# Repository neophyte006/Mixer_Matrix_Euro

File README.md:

View this project on [CADLAB.io](https://cadlab.io/project/1232). 

# Mixer_Matrix_Euro

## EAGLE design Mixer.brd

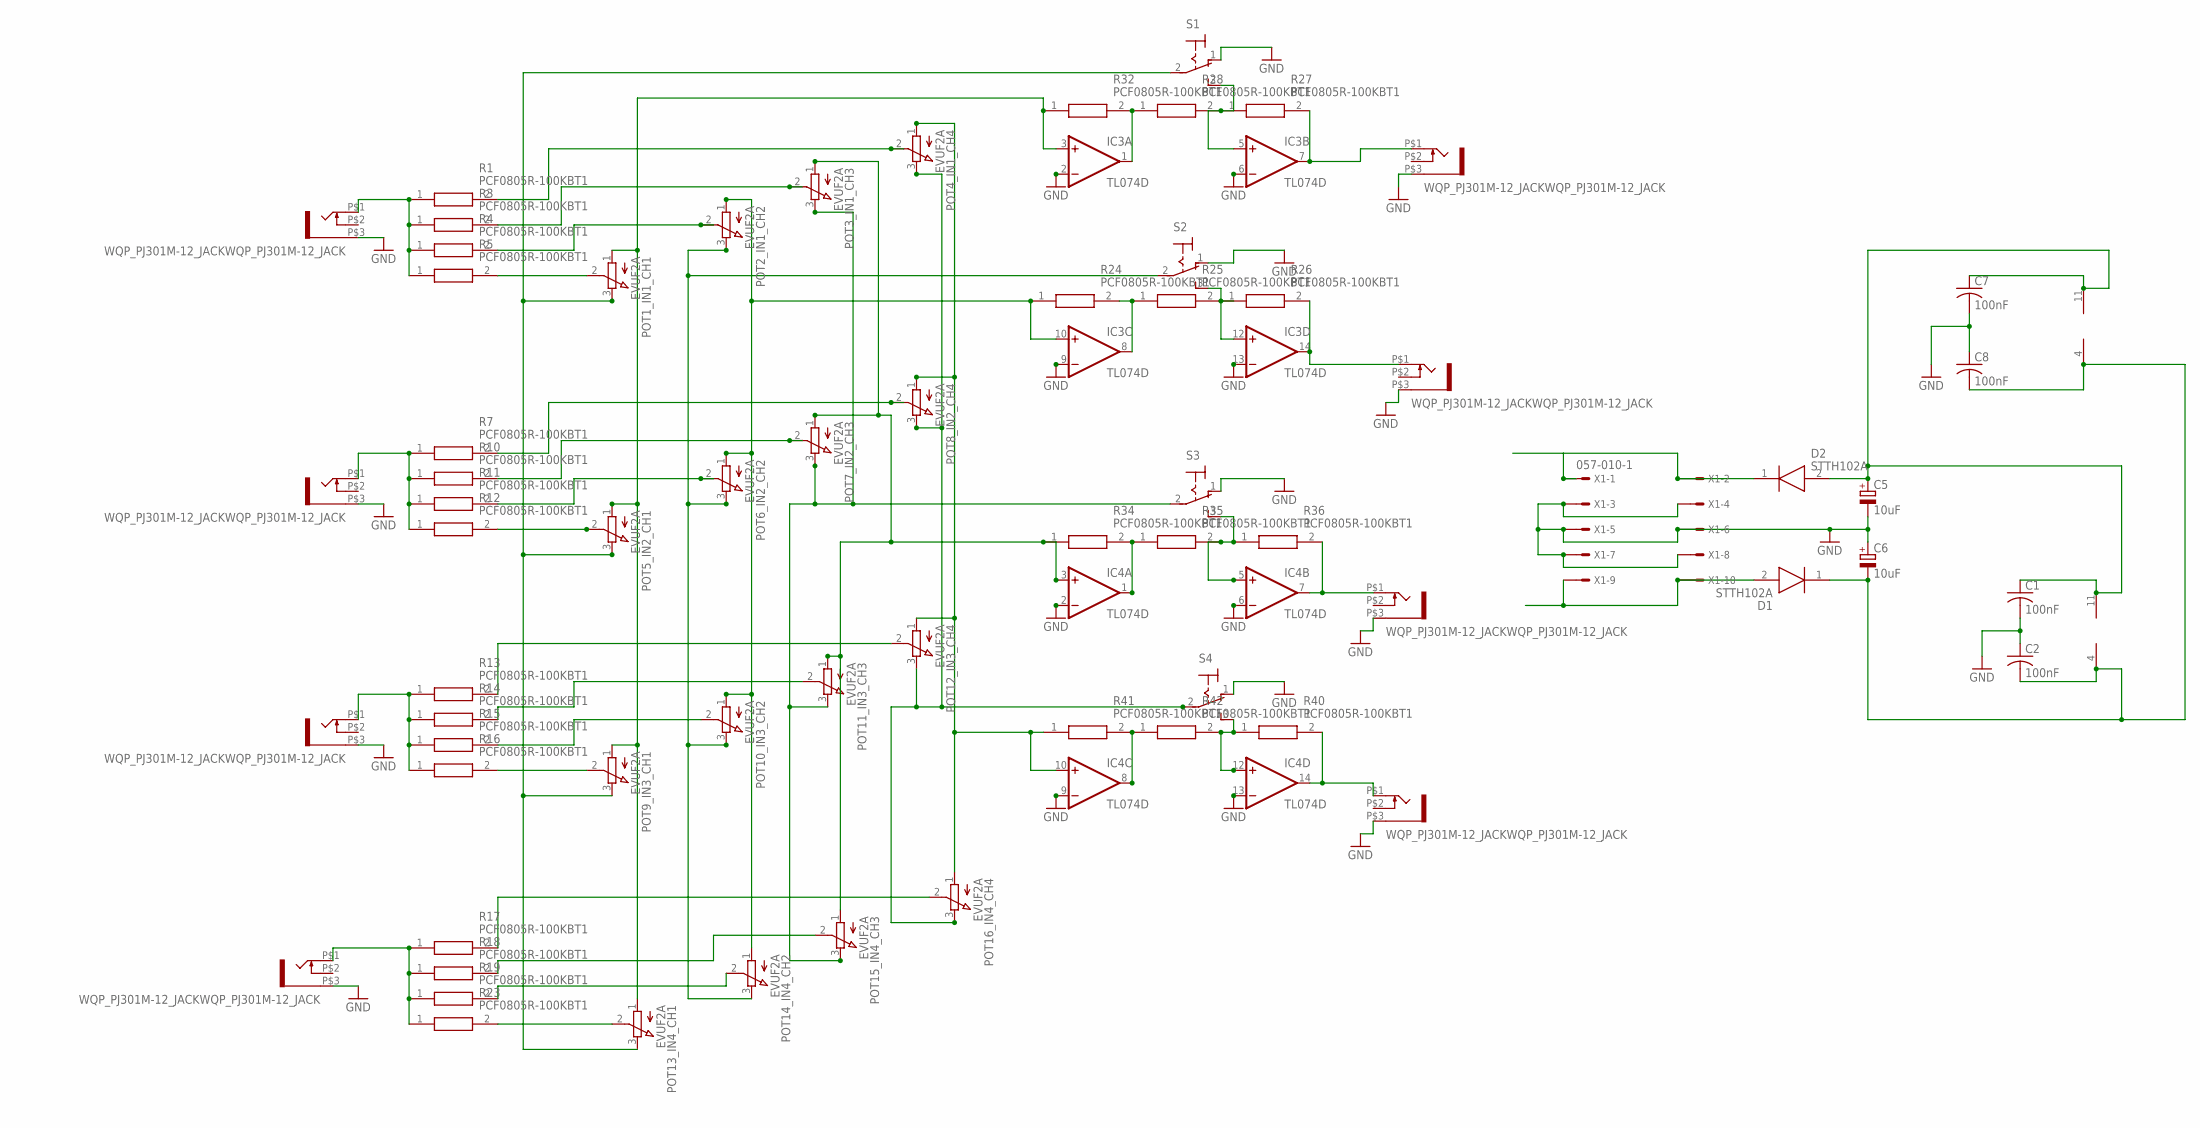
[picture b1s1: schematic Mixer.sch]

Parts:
C1, C2, C7, C8: 100nF; C0805K
C5, C6: 10uF; 153CLV-0605
D1, D2: STTH102A; DIOM5126X265N
IC3, IC4: TL074D; SO14
INPUT_1, INPUT_2, INPUT_3, INPUT_4: WQP_PJ301M-12_JACKWQP_PJ301M-12_JACK; JACK-3.5
OUTPUT_1, OUTPUT_2, OUTPUT_3, OUTPUT_4: WQP_PJ301M-12_JACKWQP_PJ301M-12_JACK; JACK-3.5
POT1_IN1_CH1, POT2_IN1_CH2, POT3_IN1_CH3, POT4_IN1_CH4, POT5_IN2_CH1, POT6_IN2_CH2, POT7_IN2_CH3, POT8_IN2_CH4, POT9_IN3_CH1, POT10_IN3_CH2, POT11_IN3_CH3, POT12_IN3_CH4, POT13_IN4_CH1, POT14_IN4_CH2, POT15_IN4_CH3, POT16_IN4_CH4: EVUF2A; EVUF
R1, R3, R4, R5, R7, R10, R11, R12, R13, R14, R15, R16, R17, R18, R19, R23, R24, R25, R26, R27, R28, R32, R34, R35, R36, R40, R41, R42: PCF0805R-100KBT1; RESC2012X65N
S1, S2, S3, S4: M9040P
X1: 057-010-1

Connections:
GND: C1.2, C2.1, C5.-, C6.+, C7.2, C8.1, IC3.2 (-IN), IC3.6 (-IN), IC3.9 (-IN), IC3.13 (-IN), IC4.2 (-IN), IC4.6 (-IN), IC4.9 (-IN), IC4.13 (-IN), INPUT_1.P$3 (1), INPUT_2.P$3 (1), INPUT_3.P$3 (1), INPUT_4.P$3 (1), OUTPUT_1.P$3 (1), OUTPUT_2.P$3 (1), OUTPUT_3.P$3 (1), OUTPUT_4.P$3 (1), S1.1 (O), S2.1 (O), S3.1 (O), S4.1 (O), X1.3, X1.4, X1.5, X1.6, X1.7, X1.8
unnamed: INPUT_2.P$1 (2), R7.1, R10.1, R11.1, R12.1
unnamed: POT13_IN4_CH1.2 (S), R23.2
unnamed: POT14_IN4_CH2.2 (S), R19.2
unnamed: POT15_IN4_CH3.2 (S), R18.2
unnamed: POT16_IN4_CH4.2 (S), R17.2
unnamed: IC3.1 (OUT), R28.1, R32.2
unnamed: IC3.10 (+IN), POT2_IN1_CH2.1 (A), POT6_IN2_CH2.1 (A), POT10_IN3_CH2.1 (A), POT14_IN4_CH2.1 (A), R24.1
unnamed: IC4.14 (OUT), OUTPUT_4.P$1 (2), R40.2
unnamed: POT5_IN2_CH1.2 (S), R12.2
unnamed: POT6_IN2_CH2.2 (S), R11.2
unnamed: POT7_IN2_CH3.2 (S), R10.2
unnamed: POT8_IN2_CH4.2 (S), R7.2
unnamed: IC3.8 (OUT), R24.2, R25.1
unnamed: IC4.1 (OUT), R34.2, R35.1
unnamed: D1.2 (A), X1.9, X1.10
unnamed: C1.1, C5.+, C7.1, D2.2 (A), IC3.11 (V-), IC4.11 (V-)
unnamed: POT1_IN1_CH1.2 (S), R5.2
unnamed: POT2_IN1_CH2.2 (S), R4.2
unnamed: POT2_IN1_CH2.3 (E), POT6_IN2_CH2.3 (E), POT10_IN3_CH2.3 (E), POT14_IN4_CH2.3 (E), S2.2
unnamed: IC3.12 (+IN), R25.2, R26.1, S2.3 (S)
unnamed: POT1_IN1_CH1.3 (E), POT5_IN2_CH1.3 (E), POT9_IN3_CH1.3 (E), POT13_IN4_CH1.3 (E), S1.2
unnamed: IC3.3 (+IN), POT1_IN1_CH1.1 (A), POT5_IN2_CH1.1 (A), POT9_IN3_CH1.1 (A), POT13_IN4_CH1.1 (A), R32.1
unnamed: IC3.5 (+IN), R27.1, R28.2, S1.3 (S)
unnamed: IC3.7 (OUT), OUTPUT_1.P$1 (2), R27.2
unnamed: IC3.14 (OUT), OUTPUT_2.P$1 (2), R26.2
unnamed: D2.1 (K), X1.1, X1.2
unnamed: IC4.12 (+IN), R40.1, R42.2, S4.3 (S)
unnamed: POT3_IN1_CH3.3 (E), POT7_IN2_CH3.3 (E), POT11_IN3_CH3.3 (E), POT15_IN4_CH3.3 (E), S3.2
unnamed: IC4.3 (+IN), POT3_IN1_CH3.1 (A), POT7_IN2_CH3.1 (A), POT11_IN3_CH3.1 (A), POT15_IN4_CH3.1 (A), R34.1
unnamed: IC4.5 (+IN), R35.2, R36.1, S3.3 (S)
unnamed: IC4.7 (OUT), OUTPUT_3.P$1 (2), R36.2
unnamed: INPUT_1.P$1 (2), R1.1, R3.1, R4.1, R5.1
unnamed: POT3_IN1_CH3.2 (S), R3.2
unnamed: POT4_IN1_CH4.2 (S), R1.2
unnamed: C2.2, C6.-, C8.2, D1.1 (K), IC3.4 (V+), IC4.4 (V+)
unnamed: POT9_IN3_CH1.2 (S), R16.2
unnamed: POT10_IN3_CH2.2 (S), R15.2
unnamed: POT11_IN3_CH3.2 (S), R14.2
unnamed: POT12_IN3_CH4.2 (S), R13.2
unnamed: IC4.10 (+IN), POT4_IN1_CH4.1 (A), POT8_IN2_CH4.1 (A), POT12_IN3_CH4.1 (A), POT16_IN4_CH4.1 (A), R41.1
unnamed: IC4.8 (OUT), R41.2, R42.1
unnamed: INPUT_3.P$1 (2), R13.1, R14.1, R15.1, R16.1
unnamed: INPUT_4.P$1 (2), R17.1, R18.1, R19.1, R23.1
unnamed: POT4_IN1_CH4.3 (E), POT8_IN2_CH4.3 (E), POT12_IN3_CH4.3 (E), POT16_IN4_CH4.3 (E), S4.2

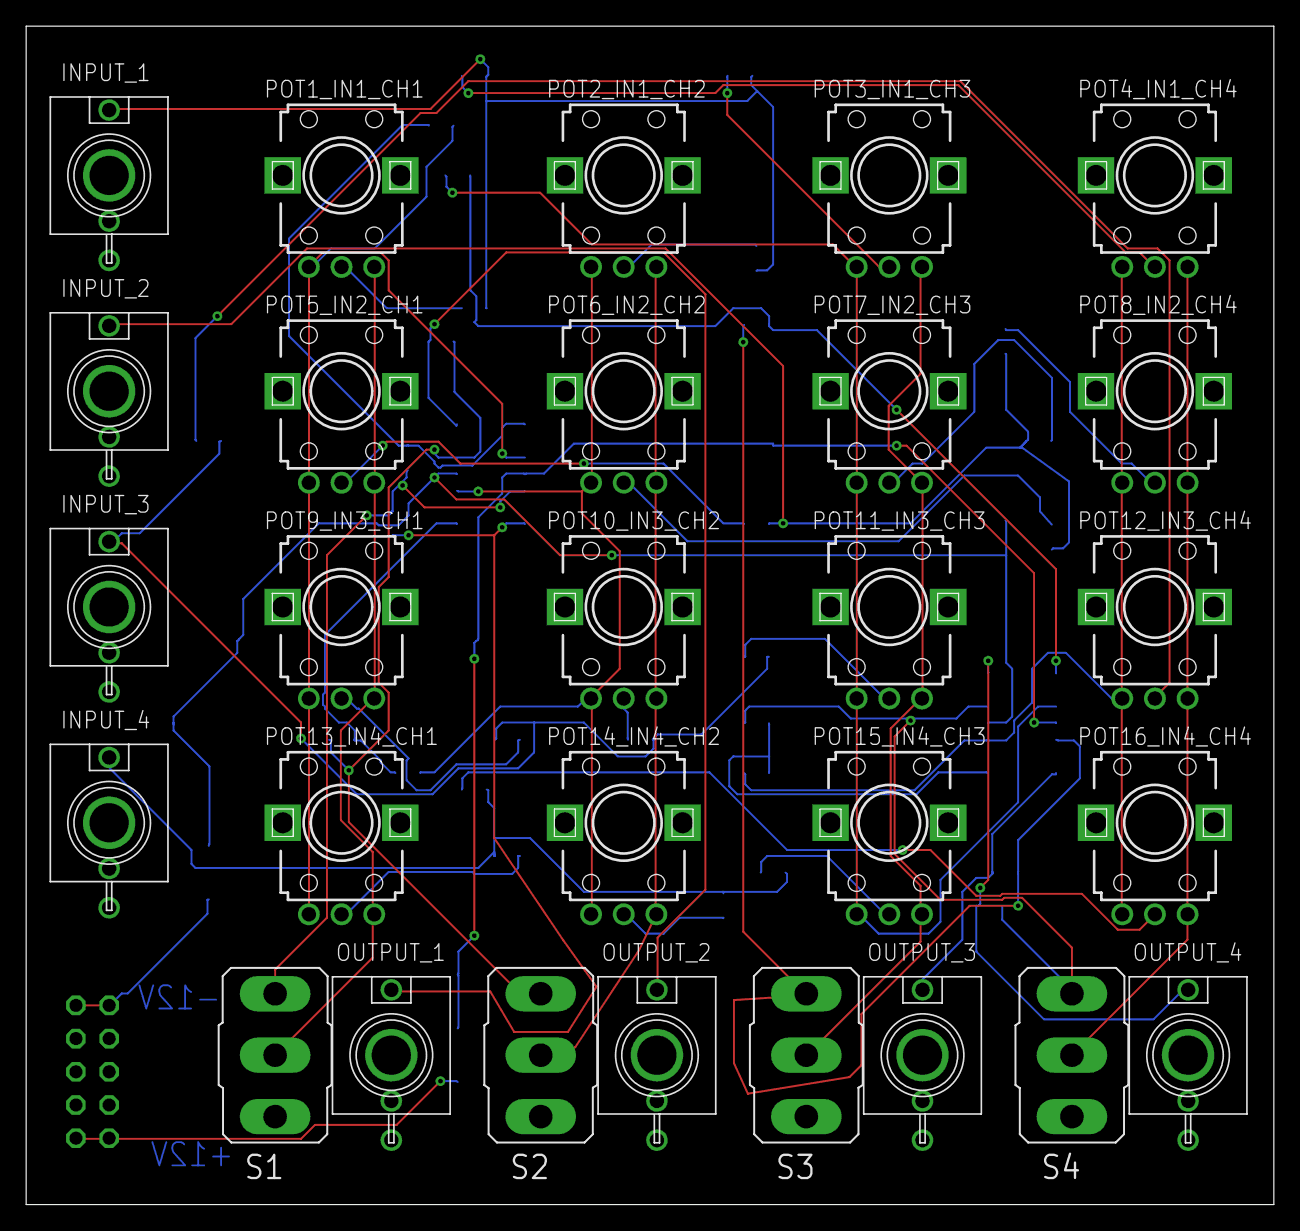
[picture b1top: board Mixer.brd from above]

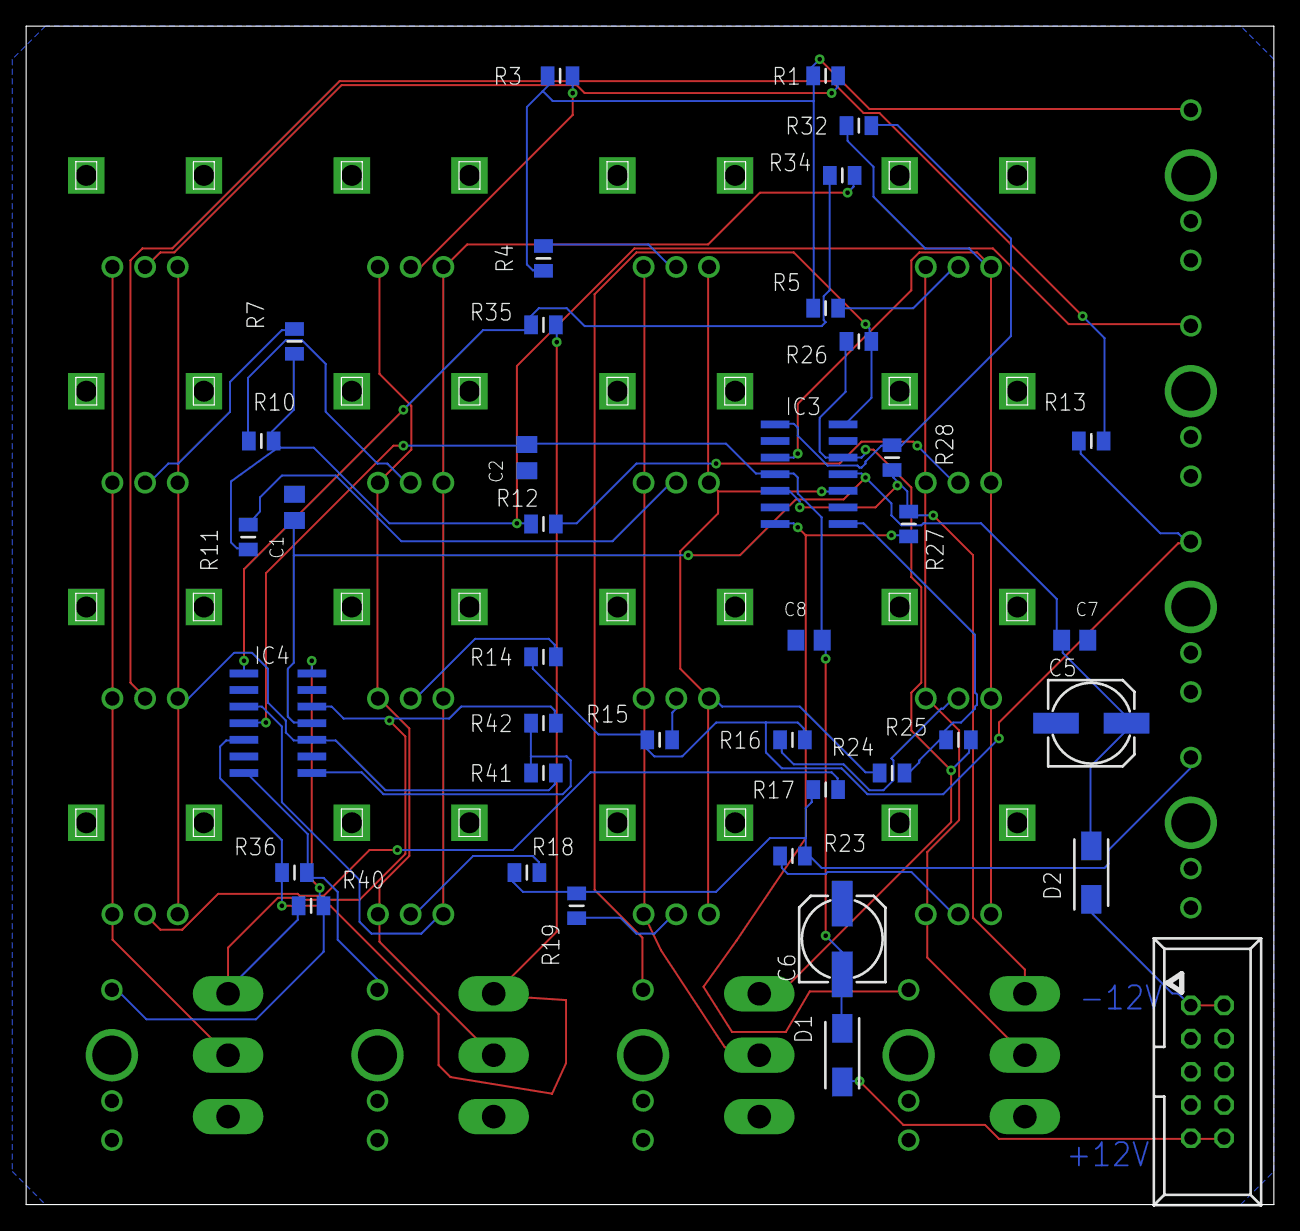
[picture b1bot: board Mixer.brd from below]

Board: 2 copper layers, 95.5 x 90.2 mm, 67 parts (39 on the bottom side), 45 nets.

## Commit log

2018-07-23 Backlink to CADLAB.io has been added.
